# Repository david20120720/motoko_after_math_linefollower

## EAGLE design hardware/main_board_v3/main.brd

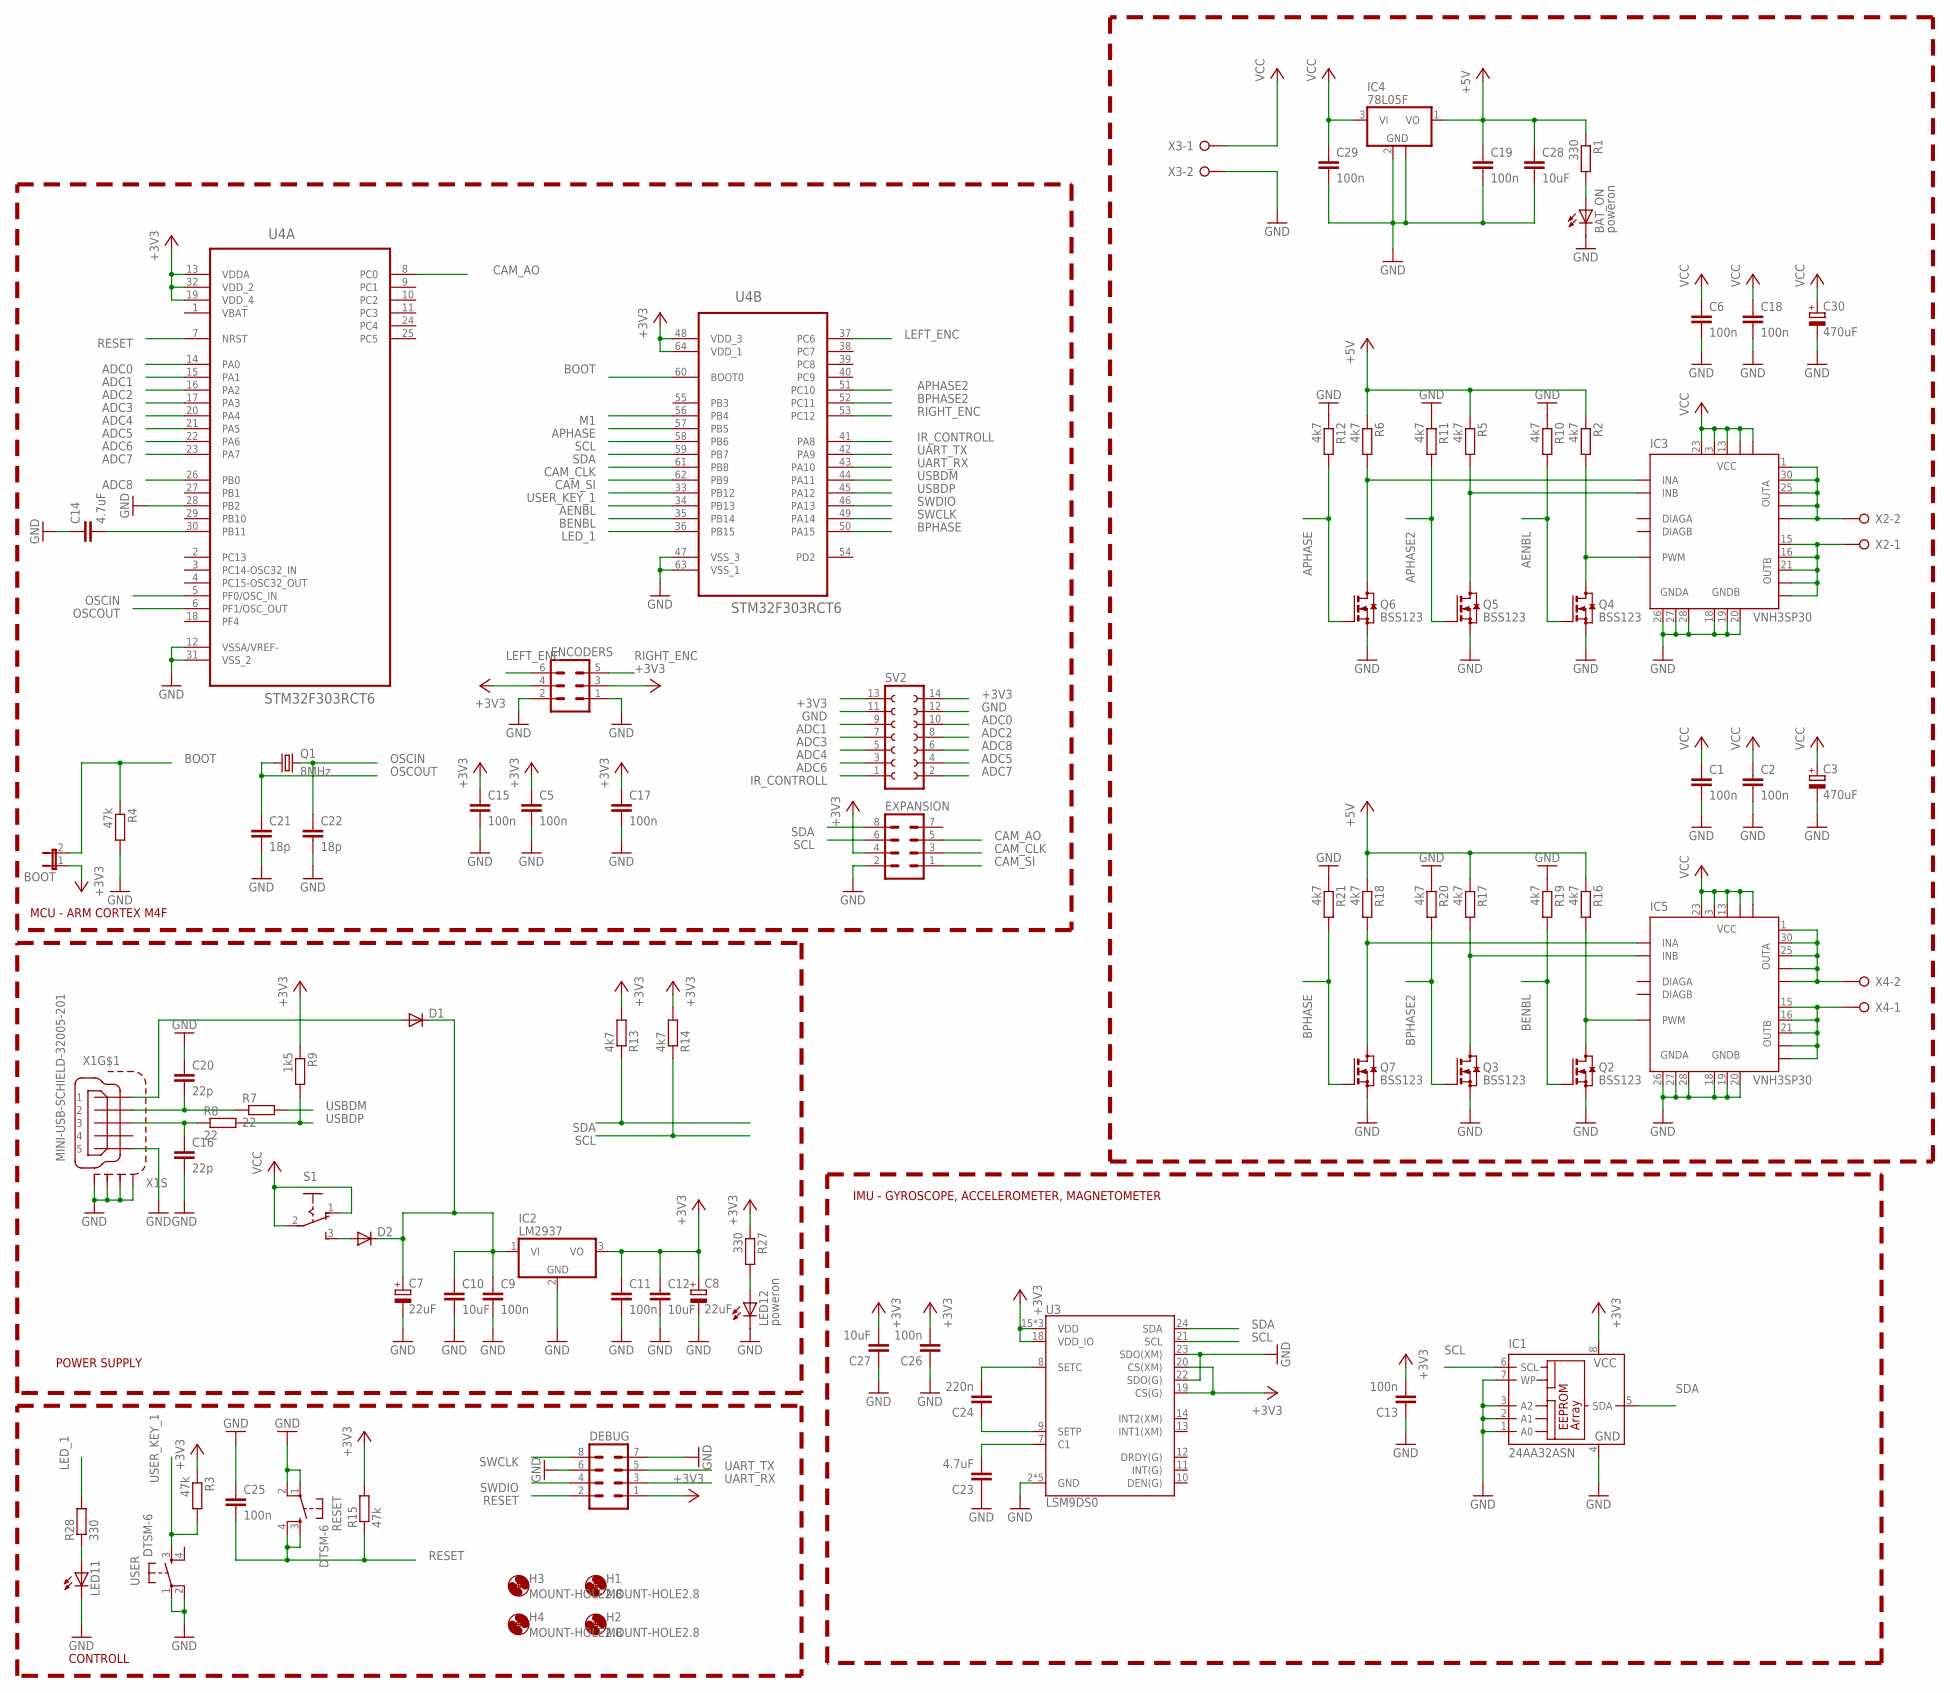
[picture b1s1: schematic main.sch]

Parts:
BAT_ON: poweron; CHIPLED_1206
BOOT: JP1E; JP1
C1, C2, C5, C6, C9, C11, C13, C15, C17, C18, C19, C25, C26, C29: 100n; C0805
C3, C30: 470uF; 140CLH-1014
C7, C8: 22uF; 153CLV-0505
C10, C12, C27, C28: 10uF; C0805
C14, C23: 4.7uF; C0805
C16, C20: 22p; C0805
C21, C22: 18p; C0805
C24: 220n; C0805
D1, D2: DIODE-SMB; SMB
DEBUG: MA04-2
ENCODERS: MA03-2
EXPANSION: MA04-2
H1, H2, H3, H4: MOUNT-HOLE2.8; 2,8
IC1: 24AA32ASN; SO-08
IC2: LM2937; TO263-3
IC3, IC5: VNH3SP30; MULTIPOWERSO-30
IC4: 78L05F; SOT89
LED11: LEDCHIPLED_1206; CHIPLED_1206
LED12: poweron; CHIPLED_1206
Q1: 8MHz; CTS406
Q2, Q3, Q4, Q5, Q6, Q7: BSS123; SOT23
R1, R27, R28: 330; M0805
R2, R5, R6, R10, R11, R12, R13, R14, R16, R17, R18, R19, R20, R21: 4k7; M0805
R3, R4, R15: 47k; M0805
R7, R8: 22; M0805
R9: 1k5; M0805
RESET: DTSM-6
S1: 255SB
SV2: FE07-2
U3: LSM9DS0; LGA-24
U4: STM32F303RCT6; QFP50P1200X1200X160-64N
USER: DTSM-6
X1: MINI-USB-SCHIELD-32005-201; 32005-201
X2, X3, X4: W237-02P; W237-132

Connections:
+3V3: BOOT.1, C5.1, C8.+, C11.1, C12.1, C13.2, C15.1, C17.1, C26.2, C27.2, DEBUG.1, ENCODERS.3, ENCODERS.4, EXPANSION.4, IC1.8 (VCC), IC2.3 (VO), R3.1, R9.1, R13.2, R14.2, R15.2, R27.1, SV2.13, SV2.14, U3.15 (VDD), U3.16 (VDD), U3.17 (VDD), U3.18 (VDD_IO), U3.19 (CS(G)), U3.20 (CS(XM)), U4.13 (VDDA), U4.19 (VDD_4), U4.32 (VDD_2), U4.48 (VDD_3), U4.64 (VDD_1)
+5V: C19.1, C28.1, IC4.1 (VO), R1.1, R2.1, R5.1, R6.1, R16.1, R17.1, R18.1; also elsewhere on the board
ADC0: SV2.10, U4.14 (PA0)
ADC1: SV2.9, U4.15 (PA1)
ADC2: SV2.8, U4.16 (PA2)
ADC3: SV2.7, U4.17 (PA3)
ADC4: SV2.5, U4.20 (PA4)
ADC5: SV2.4, U4.21 (PA5)
ADC6: SV2.3, U4.22 (PA6)
ADC7: SV2.2, U4.23 (PA7)
ADC8: SV2.6, U4.26 (PB0)
AENBL: Q4.1 (G), R10.2, U4.34 (PB13)
APHASE: Q6.1 (G), R12.2, U4.57 (PB5)
APHASE2: Q5.1 (G), R11.2, U4.51 (PC10)
BENBL: Q2.1 (G), R19.2, U4.35 (PB14)
BOOT: BOOT.2, R4.1, U4.60 (BOOT0)
BPHASE: Q7.1 (G), R21.2, U4.50 (PA15), U4.54 (PD2)
BPHASE2: Q3.1 (G), R20.2, U4.52 (PC11)
CAM_AO: EXPANSION.5, U4.8 (PC0)
CAM_CLK: EXPANSION.3, U4.61 (PB8)
CAM_SI: EXPANSION.1, U4.62 (PB9)
GND: BAT_ON.C, C1.2, C2.2, C3.-, C5.2, C6.2, C7.-, C8.-, C9.2, C10.2, C11.2, C12.2, C13.1, C14.1, C15.2, C16.2, C17.2, C18.2, C19.2, C20.1, C21.2, C22.2, C23.1, C25.1, C26.1, C27.1, C28.2, C29.2, C30.-, DEBUG.6, DEBUG.7, ENCODERS.1, ENCODERS.2, EXPANSION.2, IC1.1 (A0), IC1.2 (A1), IC1.3 (A2), IC1.4 (GND), IC1.7 (WP), IC2.2 (GND), IC3.18 (GNDB), IC3.19 (GNDB), IC3.20 (GNDB), IC3.26 (GNDA), IC3.27 (GNDA), IC3.28 (GNDA), IC4.2 (GND), IC4.2@1 (GND), IC5.18 (GNDB), IC5.19 (GNDB), IC5.20 (GNDB), IC5.26 (GNDA), IC5.27 (GNDA), IC5.28 (GNDA), LED11.C, LED12.C, Q2.2 (S), Q3.2 (S), Q4.2 (S), Q5.2 (S), Q6.2 (S), Q7.2 (S), R4.2, R10.1, R11.1, R12.1, R19.1, R20.1, R21.1, RESET.1, RESET.2, SV2.11, SV2.12, U3.2 (GND), U3.3 (GND), U3.4 (GND), U3.5 (GND), U3.6 (GND), U3.22 (SDO(G)), U3.23 (SDO(XM)), U4.12 (VSSA/VREF-), U4.28 (PB2), U4.31 (VSS_2), U4.47 (VSS_3), U4.63 (VSS_1), USER.1, USER.2, X1.5, X1.M1 (S1), X1.M2 (S2), X1.M3 (S3), X1.M4 (S4), X3.2; also elsewhere on the board
IR_CONTROLL: SV2.1, U4.41 (PA8)
LED_1: R28.2, U4.36 (PB15)
LEFT_ENC: ENCODERS.6, U4.37 (PC6)
M1: U4.56 (PB4)
MOTOR_ENABLE: U4.38 (PC7); also elsewhere on the board
M_ENABLE: IC3.6 (DIAGA), IC3.10 (DIAGB), IC5.6 (DIAGA), IC5.10 (DIAGB); also elsewhere on the board
unnamed: D2.A, S1.3 (S)
unnamed: C7.+, C9.1, C10.1, D1.C, D2.C, IC2.1 (VI)
unnamed: BAT_ON.A, R1.2
unnamed: IC5.5 (INA), Q7.3 (D), R18.2
unnamed: IC5.11 (INB), Q3.3 (D), R17.2
unnamed: C23.2, U3.7 (C1)
unnamed: C24.2, U3.8 (SETC)
unnamed: IC5.8 (PWM), Q2.3 (D), R16.2
unnamed: IC5.1 (OUTA), IC5.25 (OUTA), IC5.30 (OUTA), IC5.OUTA, IC5.OUTA@1 (OUTA), X4.2
unnamed: C24.1, U3.9 (SETP)
unnamed: IC5.15 (OUTB), IC5.16 (OUTB), IC5.21 (OUTB), IC5.OUTB, IC5.OUTB@1 (OUTB), X4.1
unnamed: C14.2, U4.30 (PB11)
unnamed: IC3.5 (INA), Q6.3 (D), R6.2
unnamed: IC3.11 (INB), Q5.3 (D), R5.2
unnamed: IC3.8 (PWM), Q4.3 (D), R2.2
unnamed: IC3.1 (OUTA), IC3.25 (OUTA), IC3.30 (OUTA), IC3.OUTA, IC3.OUTA@1 (OUTA), X2.2
unnamed: LED12.A, R27.2
unnamed: IC3.15 (OUTB), IC3.16 (OUTB), IC3.21 (OUTB), IC3.OUTB, IC3.OUTB@1 (OUTB), X2.1
unnamed: LED11.A, R28.1
unnamed: C20.2, R7.1, X1.2
unnamed: C16.1, R8.1, X1.3
unnamed: D1.A, X1.1
OSCIN: C22.1, Q1.3 (2), U4.5 (PF0/OSC_IN)
OSCOUT: C21.1, Q1.1, U4.6 (PF1/OSC_OUT)
RESET: C25.2, DEBUG.2, R15.1, RESET.3, RESET.4, U4.7 (NRST)
RIGHT_ENC: ENCODERS.5, U4.53 (PC12)
SCL: EXPANSION.6, IC1.6 (SCL), R14.1, U3.21 (SCL), U4.58 (PB6)
SDA: EXPANSION.8, IC1.5 (SDA), R13.1, U3.24 (SDA), U4.59 (PB7)
SWCLK: DEBUG.8, U4.49 (PA14)
SWDIO: DEBUG.4, U4.46 (PA13)
UART_RX: DEBUG.3, U4.43 (PA10)
UART_TX: DEBUG.5, U4.42 (PA9)
USBDM: R7.2, U4.44 (PA11)
USBDP: R8.2, R9.2, U4.45 (PA12)
USER_KEY_1: R3.2, U4.33 (PB12), USER.3
VBAT: U4.1 (VBAT)
VCC: C1.1, C2.1, C3.+, C6.1, C18.1, C29.1, C30.+, IC3.3 (VCC), IC3.13 (VCC), IC3.23 (VCC), IC3.VCC, IC3.VCC@1 (VCC), IC4.3 (VI), IC5.3 (VCC), IC5.13 (VCC), IC5.23 (VCC), IC5.VCC, IC5.VCC@1 (VCC), S1.1 (O), S1.2, X3.1

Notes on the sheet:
POWER SUPPLY
CONTROLL
MCU - ARM CORTEX M4F
IMU - GYROSCOPE, ACCELEROMETER, MAGNETOMETER

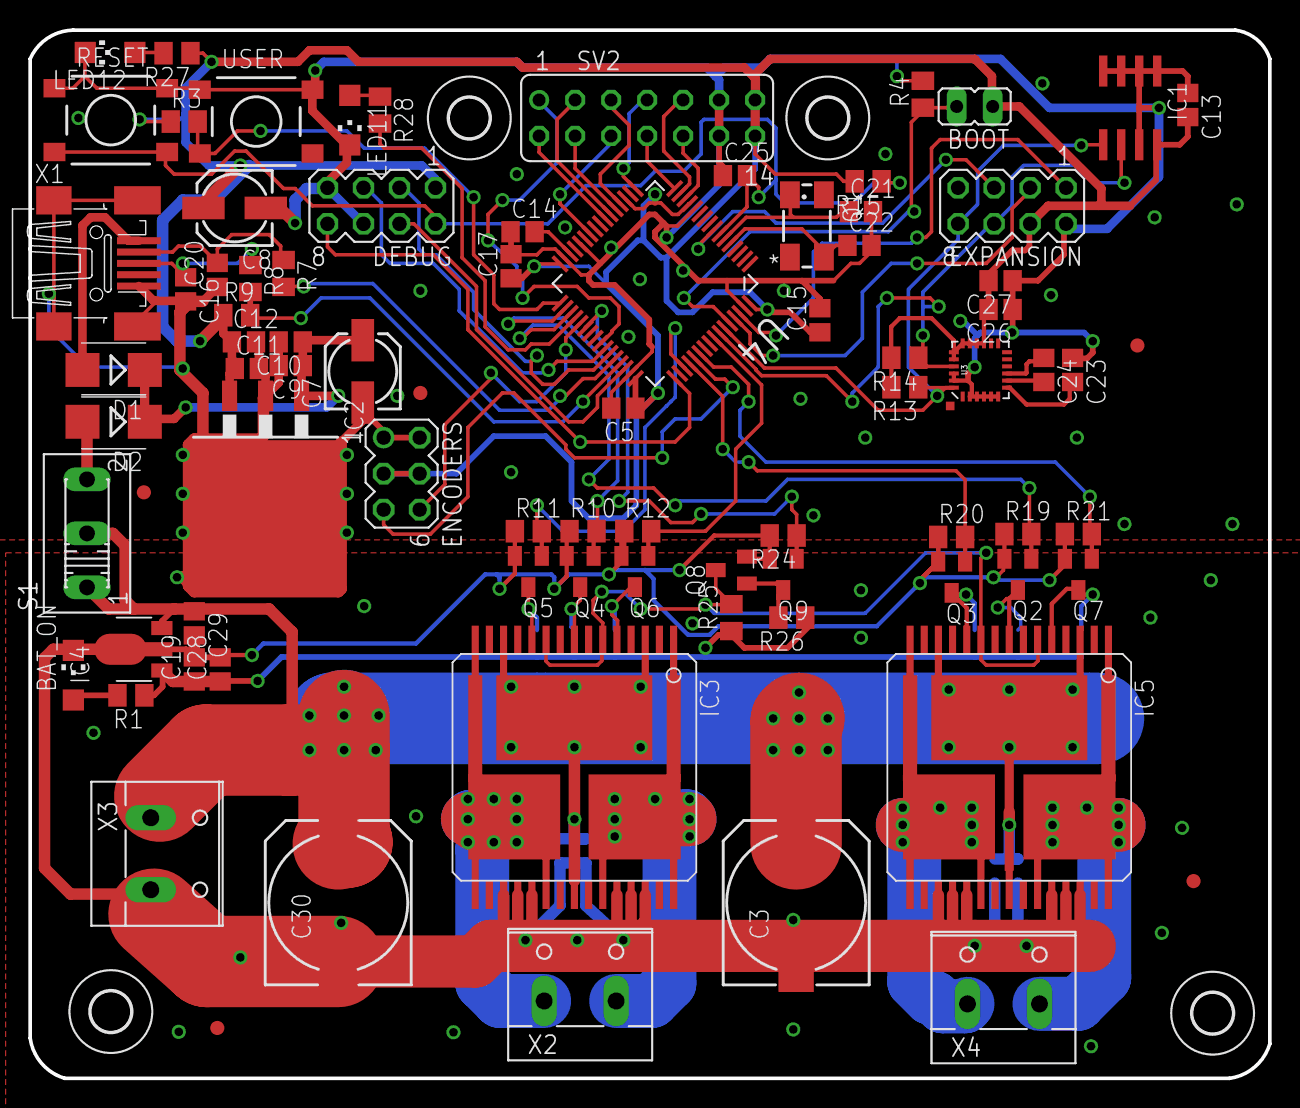
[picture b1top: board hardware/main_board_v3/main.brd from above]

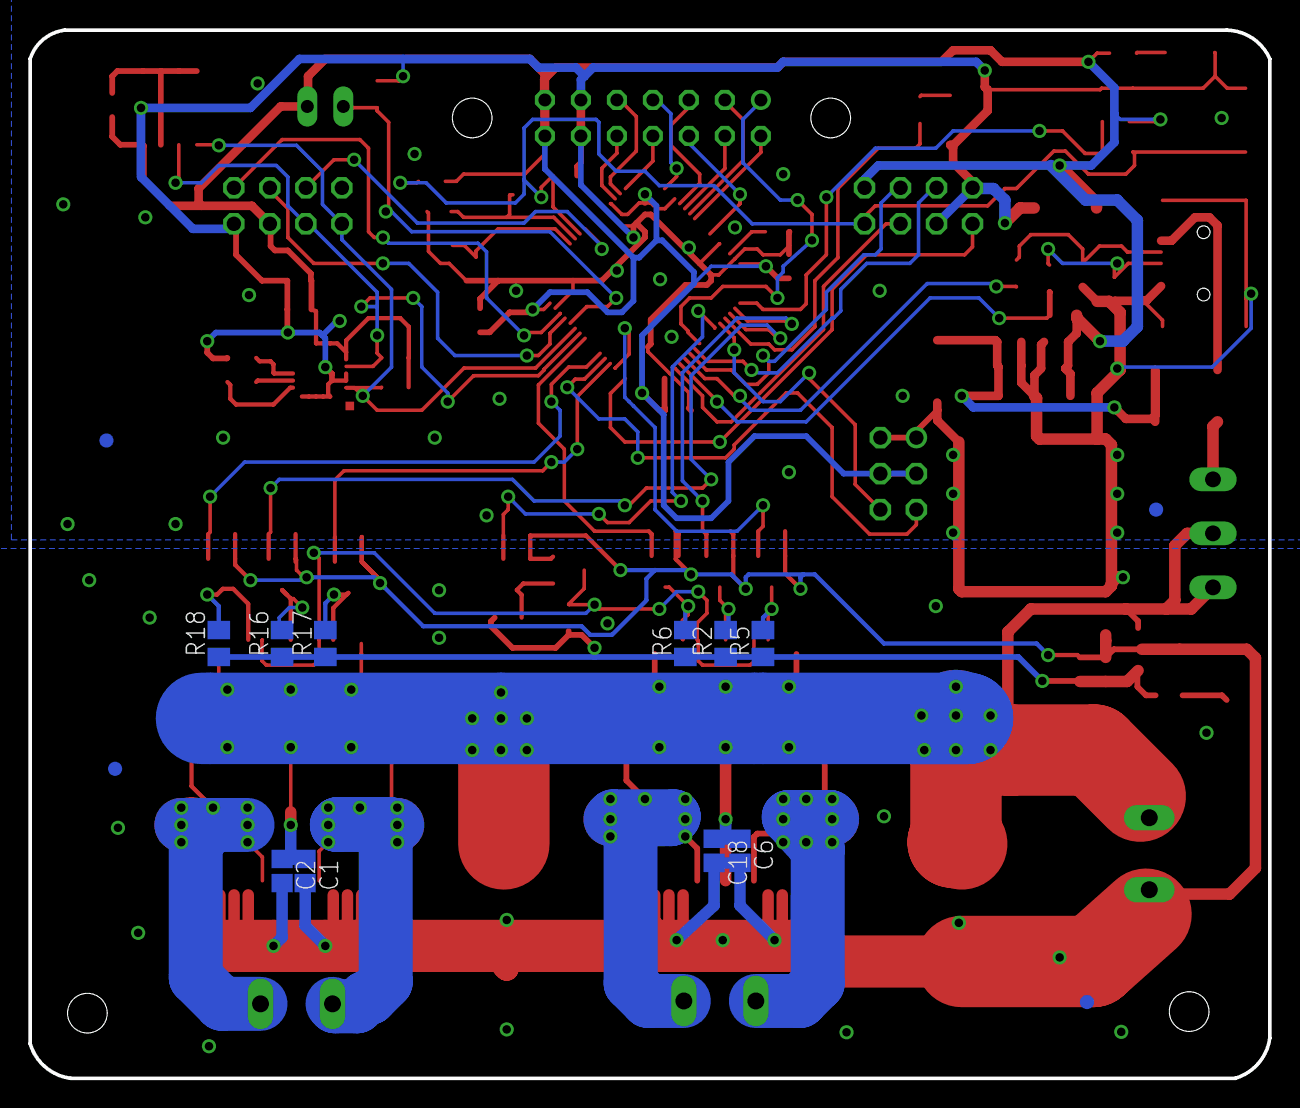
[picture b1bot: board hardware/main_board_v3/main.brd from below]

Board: 2 copper layers, 87.5 x 74.0 mm, 101 parts (14 on the bottom side), 64 nets.

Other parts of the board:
Q8, Q9: BSS123; SOT23
R24, R25, R26: 4k7; M0805
U$1, U$2, U$3, U$4, U$5, U$6, U$7, U$8, U$9: FIDUCIAL; FIDUCIAL_1MM

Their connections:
+5V: R25.1, R26.1; also elsewhere on the board
GND: Q8.2, Q9.2, R24.2; also elsewhere on the board
MOTOR_ENABLE: Q9.1, R24.1; also elsewhere on the board
M_ENABLE: Q8.3, R25.2; also elsewhere on the board
unnamed: Q8.1, Q9.3, R26.2

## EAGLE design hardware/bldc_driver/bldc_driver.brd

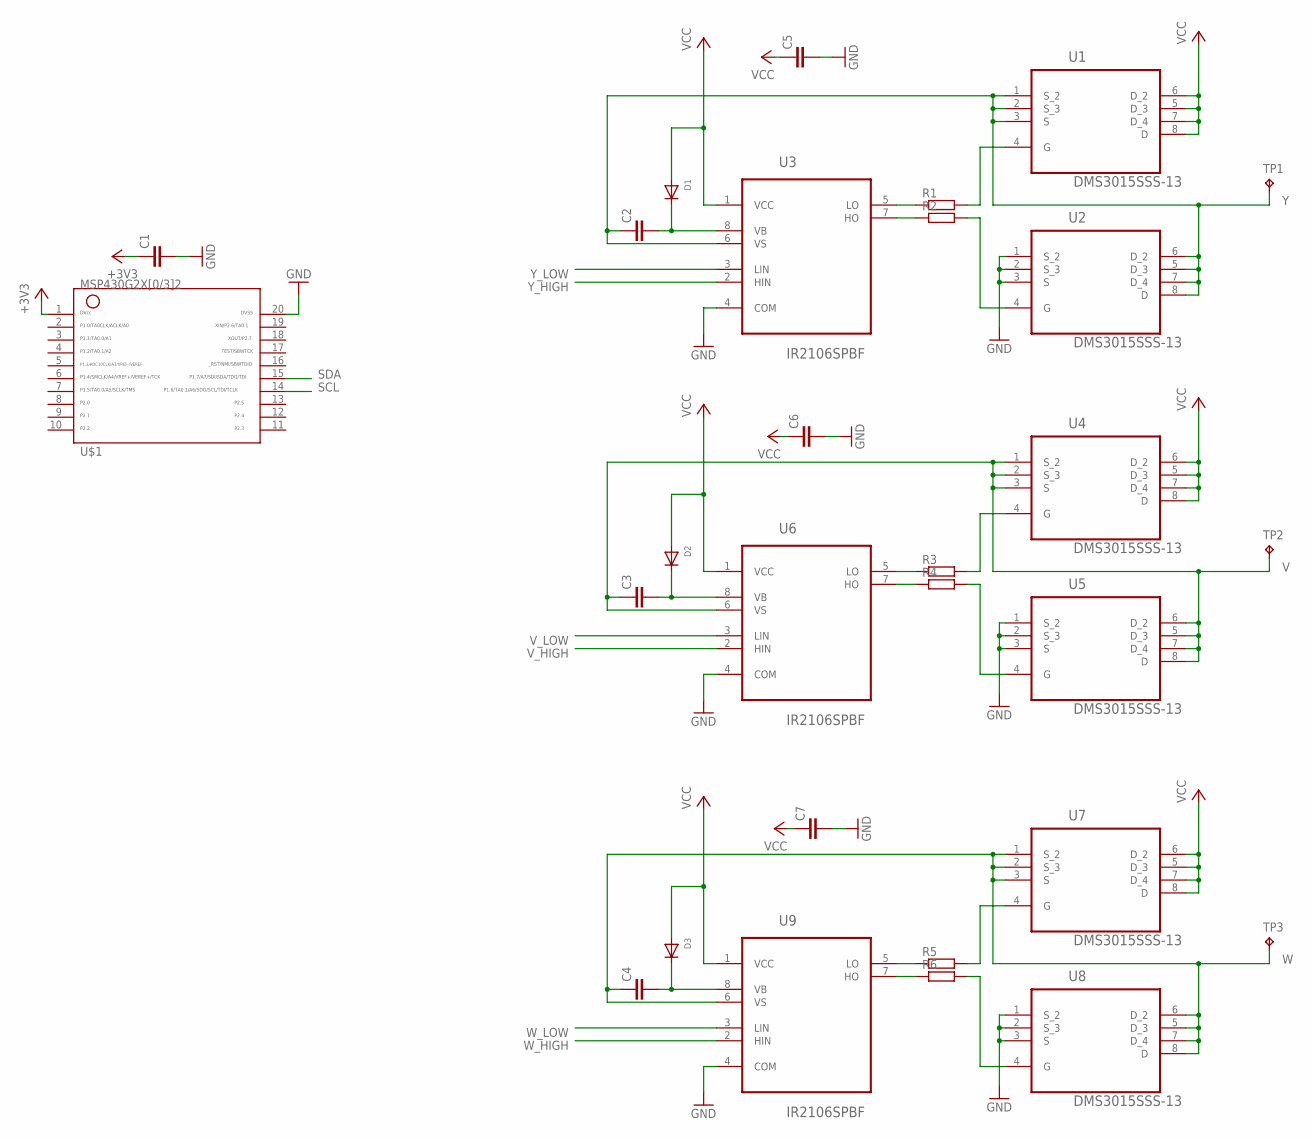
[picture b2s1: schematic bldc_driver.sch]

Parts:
C1, C2, C3, C4, C5, C6, C7: C-EUC0805; C0805
D1, D2, D3: DIODE_SOD-123FL; SOD-123FL
R1, R2, R3, R4, R5, R6: R-EU_M0805; M0805
TP1, TP2, TP3: TPTP18R; TP18R
U1, U2, U4, U5, U7, U8: DMS3015SSS-13; SOIC127P600X175-8N
U3, U6, U9: IR2106SPBF; SOIC127P600X175-8N
U$1: G2X[0/3]2---PW20; PW20

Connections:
+3V3: C1.1, U$1.1
GND: C1.2, C5.2, C6.2, C7.2, U2.1 (S_2), U2.2 (S_3), U2.3 (S), U3.4 (COM), U5.1 (S_2), U5.2 (S_3), U5.3 (S), U6.4 (COM), U8.1 (S_2), U8.2 (S_3), U8.3 (S), U9.4 (COM), U$1.20
unnamed: R1.2, U1.4 (G)
unnamed: R1.1, U3.5 (LO)
unnamed: R2.1, U3.7 (HO)
unnamed: R2.2, U2.4 (G)
unnamed: C2.2, D1.C, U3.8 (VB)
unnamed: R3.2, U4.4 (G)
unnamed: R3.1, U6.5 (LO)
unnamed: R4.1, U6.7 (HO)
unnamed: R4.2, U5.4 (G)
unnamed: C3.2, D2.C, U6.8 (VB)
unnamed: R5.2, U7.4 (G)
unnamed: R5.1, U9.5 (LO)
unnamed: R6.1, U9.7 (HO)
unnamed: R6.2, U8.4 (G)
unnamed: C4.2, D3.C, U9.8 (VB)
SCL: U$1.14
SDA: U$1.15
V: C3.1, TP2.TP, U4.1 (S_2), U4.2 (S_3), U4.3 (S), U5.5 (D_3), U5.6 (D_2), U5.7 (D_4), U5.8 (D), U6.6 (VS)
VCC: C5.1, C6.1, C7.1, D1.A, D2.A, D3.A, U1.5 (D_3), U1.6 (D_2), U1.7 (D_4), U1.8 (D), U3.1 (VCC), U4.5 (D_3), U4.6 (D_2), U4.7 (D_4), U4.8 (D), U6.1 (VCC), U7.5 (D_3), U7.6 (D_2), U7.7 (D_4), U7.8 (D), U9.1 (VCC)
V_HIGH: U6.2 (HIN)
V_LOW: U6.3 (LIN)
W: C4.1, TP3.TP, U7.1 (S_2), U7.2 (S_3), U7.3 (S), U8.5 (D_3), U8.6 (D_2), U8.7 (D_4), U8.8 (D), U9.6 (VS)
W_HIGH: U9.2 (HIN)
W_LOW: U9.3 (LIN)
Y: C2.1, TP1.TP, U1.1 (S_2), U1.2 (S_3), U1.3 (S), U2.5 (D_3), U2.6 (D_2), U2.7 (D_4), U2.8 (D), U3.6 (VS)
Y_HIGH: U3.2 (HIN)
Y_LOW: U3.3 (LIN)

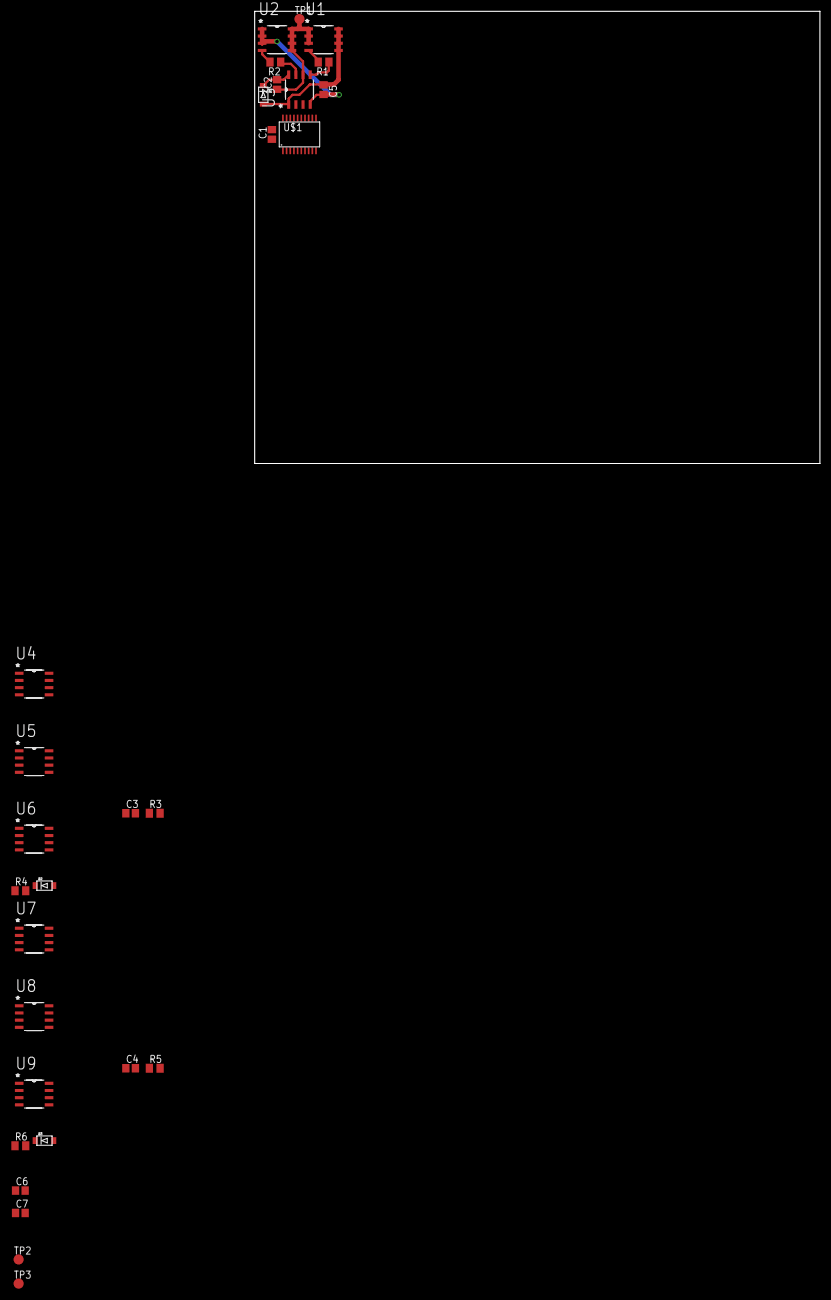
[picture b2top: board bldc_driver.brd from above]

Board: 2 copper layers, 100.0 x 80.0 mm, 29 parts (0 on the bottom side), 21 nets.

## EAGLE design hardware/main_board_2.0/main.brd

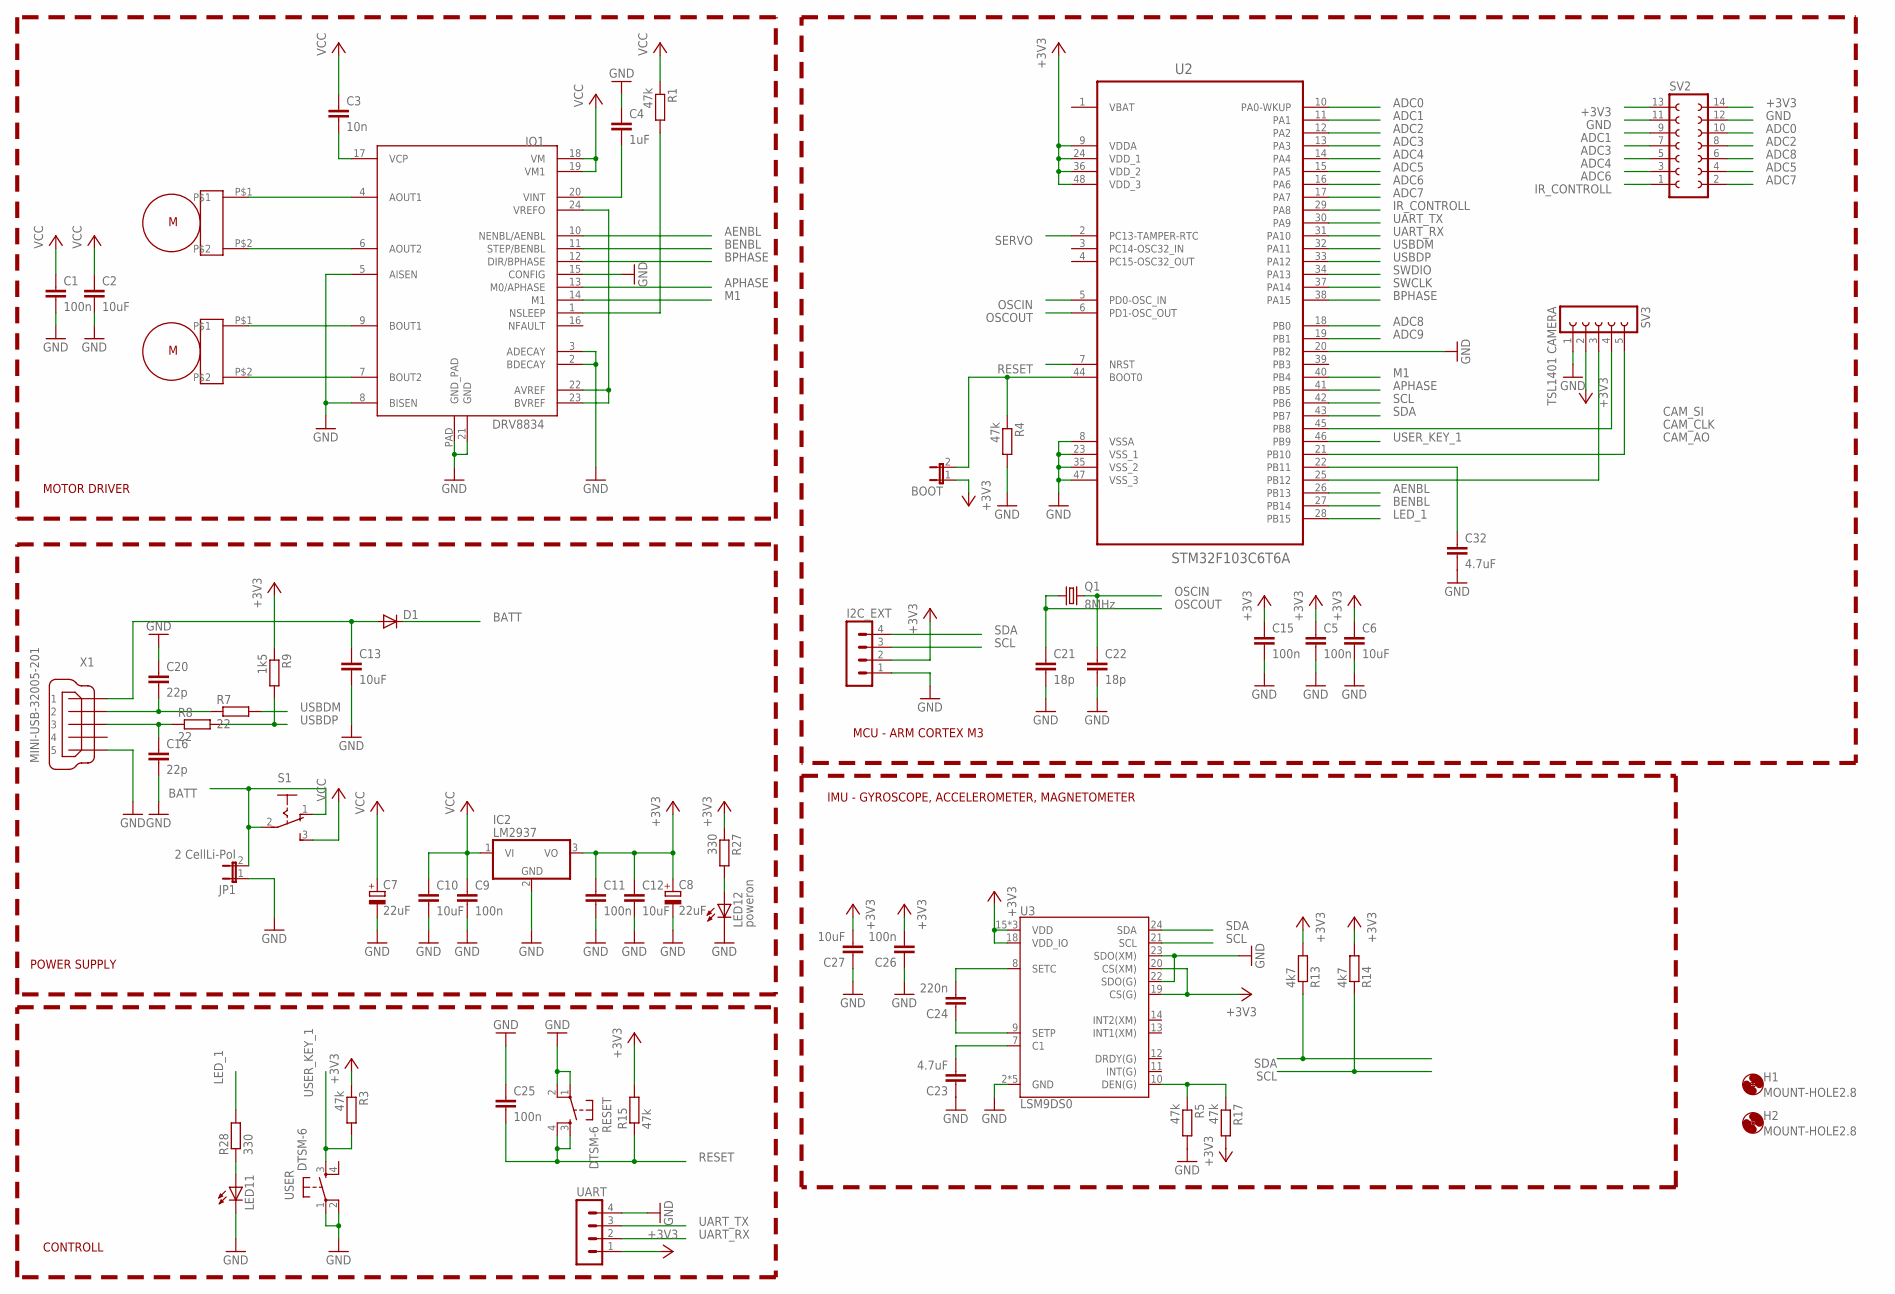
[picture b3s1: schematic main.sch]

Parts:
BOOT: JP1E; JP1
C1: 100n; C1206
C2: 10uF; C1206
C3: 10n; C1206
C4: 1uF; C1206
C5, C9, C11, C15, C25, C26: 100n; C0805
C6, C10, C12, C13, C27: 10uF; C0805
C7, C8: 22uF; 153CLV-0505
C16, C20: 22p; C0805
C21, C22: 18p; C0805
C23, C32: 4.7uF; C0805
C24: 220n; C0805
D1: DIODE-SMB; SMB
H1, H2: MOUNT-HOLE2.8; 2,8
I2C_EXT: MA04-1
IC2: LM2937; TO263-3
IO1: DRV8834; DRV8834_PCK
JP1: 2 CellLi-Pol; JP1
LED11: LEDCHIPLED_1206; CHIPLED_1206
LED12: poweron; CHIPLED_1206
Q1: 8MHz; CTS406
R1: 47k; M1206
R3, R4, R5, R15, R17: 47k; M0805
R7, R8: 22; M0805
R9: 1k5; M0805
R13, R14: 4k7; M0805
R27, R28: 330; M0805
RESET: DTSM-6
S1: 255SB
SV2: FE07-2
SV3: TSL1401 CAMERA; FE05-1
U2: STM32F103C6T6A; QFP50P900X900X160-48N
U3: LSM9DS0; LGA-24
U$1, U$2: MICRO_METAL_GEAR_MOTOR
UART: MA04-1
USER: DTSM-6
X1: MINI-USB-32005-201; 32005-201

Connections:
+3V3: BOOT.1, C5.1, C6.1, C8.+, C11.1, C12.1, C15.1, C26.2, C27.2, I2C_EXT.2, IC2.3 (VO), R3.1, R9.1, R13.2, R14.2, R15.2, R17.2, R27.1, SV2.13, SV2.14, SV3.2, U2.9 (VDDA), U2.24 (VDD_1), U2.36 (VDD_2), U2.48 (VDD_3), U3.15 (VDD), U3.16 (VDD), U3.17 (VDD), U3.18 (VDD_IO), U3.19 (CS(G)), U3.20 (CS(XM)), UART.1
ADC0: SV2.10, U2.10 (PA0-WKUP)
ADC1: SV2.9, U2.11 (PA1)
ADC2: SV2.8, U2.12 (PA2)
ADC3: SV2.7, U2.13 (PA3)
ADC4: SV2.5, U2.14 (PA4)
ADC5: SV2.4, U2.15 (PA5)
ADC6: SV2.3, U2.16 (PA6)
ADC7: SV2.2, U2.17 (PA7)
ADC8: SV2.6, U2.18 (PB0)
ADC9: U2.19 (PB1)
AENBL: IO1.10 (NENBL/AENBL), U2.26 (PB13)
APHASE: IO1.13 (M0/APHASE), U2.41 (PB5)
BATT: D1.C, JP1.2, S1.1 (O), S1.2
BENBL: IO1.11 (STEP/BENBL), U2.27 (PB14)
BPHASE: IO1.12 (DIR/BPHASE), U2.38 (PA15)
CAM_AO: SV3.3, U2.25 (PB12)
CAM_CLK: SV3.4, U2.45 (PB8)
CAM_SI: SV3.5, U2.21 (PB10)
GND: C1.2, C2.2, C4.1, C5.2, C6.2, C7.-, C8.-, C9.2, C10.2, C11.2, C12.2, C13.2, C15.2, C16.2, C20.1, C21.2, C22.2, C23.1, C25.1, C26.1, C27.1, C32.2, I2C_EXT.1, IC2.2 (GND), IO1.2 (BDECAY), IO1.3 (ADECAY), IO1.5 (AISEN), IO1.8 (BISEN), IO1.15 (CONFIG), IO1.21 (GND), IO1.PAD (GND_PAD), JP1.1, LED11.C, LED12.C, R4.2, R5.2, RESET.1, RESET.2, SV2.11, SV2.12, SV3.1, U2.8 (VSSA), U2.20 (PB2), U2.23 (VSS_1), U2.35 (VSS_2), U2.47 (VSS_3), U3.2 (GND), U3.3 (GND), U3.4 (GND), U3.5 (GND), U3.6 (GND), U3.22 (SDO(G)), U3.23 (SDO(XM)), UART.4, USER.1, USER.2, X1.5
IR_CONTROLL: SV2.1, U2.29 (PA8)
LED_1: R28.2, U2.28 (PB15)
M1: IO1.14 (M1), U2.40 (PB4)
unnamed: IO1.4 (AOUT1), U$1.P$1
unnamed: IO1.6 (AOUT2), U$1.P$2
unnamed: IO1.9 (BOUT1), U$2.P$1
unnamed: IO1.7 (BOUT2), U$2.P$2
unnamed: C3.2, IO1.17 (VCP)
unnamed: C23.2, U3.7 (C1)
unnamed: C24.2, U3.8 (SETC)
unnamed: IO1.22 (AVREF), IO1.23 (BVREF), IO1.24 (VREFO)
unnamed: IO1.1 (NSLEEP), R1.2
unnamed: C24.1, U3.9 (SETP)
unnamed: C32.1, U2.22 (PB11)
unnamed: BOOT.2, R4.1, U2.44 (BOOT0)
unnamed: R5.1, R17.1, U3.10 (DEN(G))
unnamed: C4.2, IO1.20 (VINT)
unnamed: LED12.A, R27.2
unnamed: LED11.A, R28.1
unnamed: C20.2, R7.1, X1.2
unnamed: C16.1, R8.1, X1.3
unnamed: C13.1, D1.A, X1.1
OSCIN: C22.1, Q1.3 (2), U2.5 (PD0-OSC_IN)
OSCOUT: C21.1, Q1.1, U2.6 (PD1-OSC_OUT)
RESET: C25.2, R15.1, RESET.3, RESET.4, U2.7 (NRST)
SCL: I2C_EXT.3, R14.1, U2.42 (PB6), U3.21 (SCL)
SDA: I2C_EXT.4, R13.1, U2.43 (PB7), U3.24 (SDA)
SERVO: U2.2 (PC13-TAMPER-RTC)
SWCLK: U2.37 (PA14)
SWDIO: U2.34 (PA13)
UART_RX: U2.31 (PA10), UART.2
UART_TX: U2.30 (PA9), UART.3
USBDM: R7.2, U2.32 (PA11)
USBDP: R8.2, R9.2, U2.33 (PA12)
USER_KEY_1: R3.2, U2.46 (PB9), USER.3
VBAT: U2.1 (VBAT)
VCC: C1.1, C2.1, C3.1, C7.+, C9.1, C10.1, IC2.1 (VI), IO1.18 (VM), IO1.19 (VM1), R1.1, S1.3 (S)

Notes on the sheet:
MOTOR DRIVER
POWER SUPPLY
CONTROLL
MCU - ARM CORTEX M3
IMU - GYROSCOPE, ACCELEROMETER, MAGNETOMETER

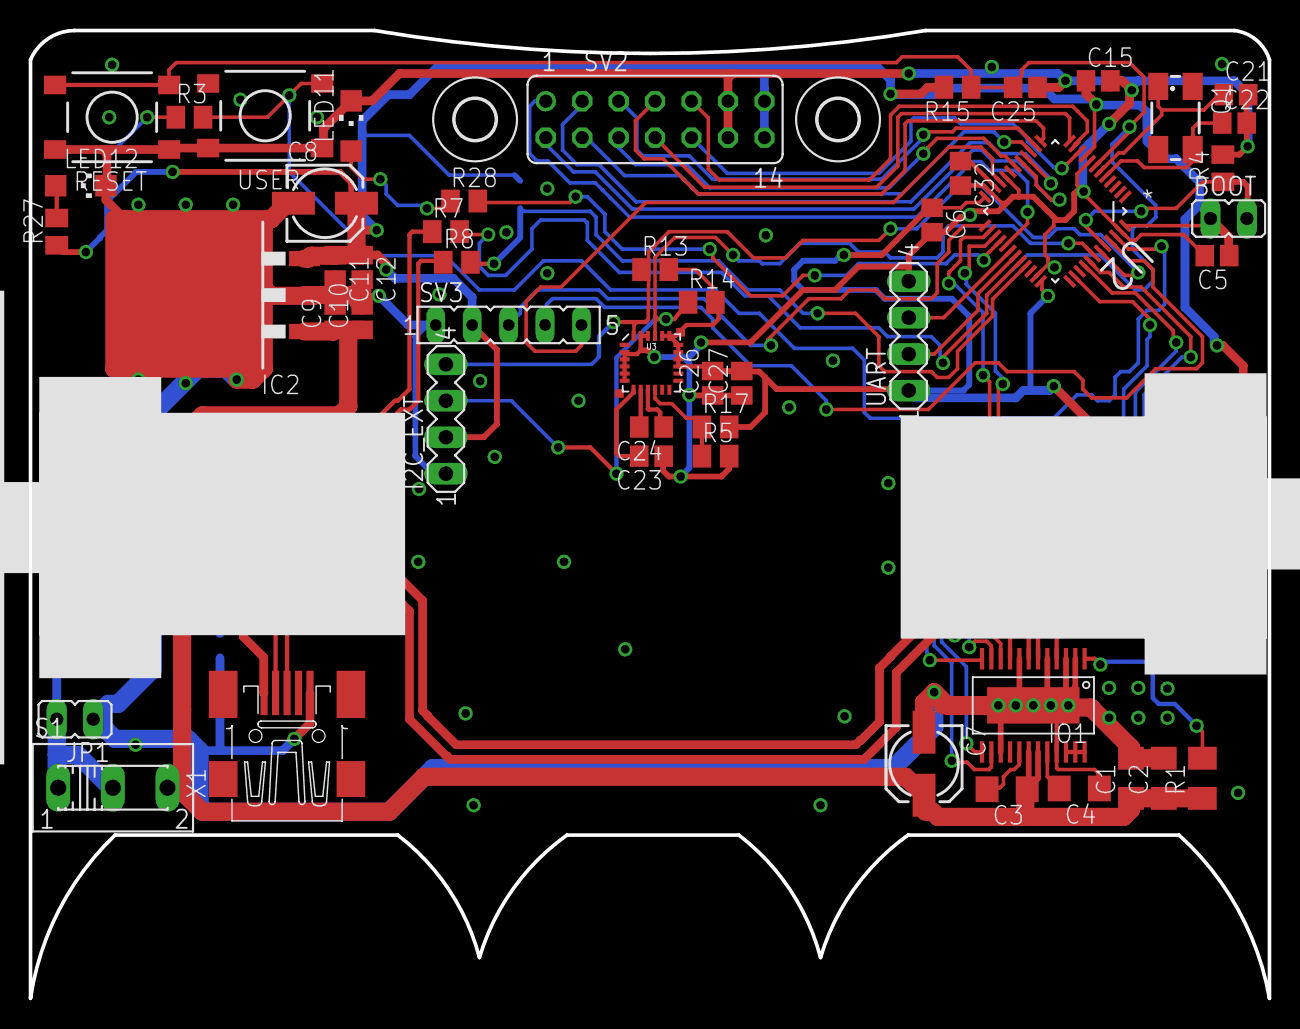
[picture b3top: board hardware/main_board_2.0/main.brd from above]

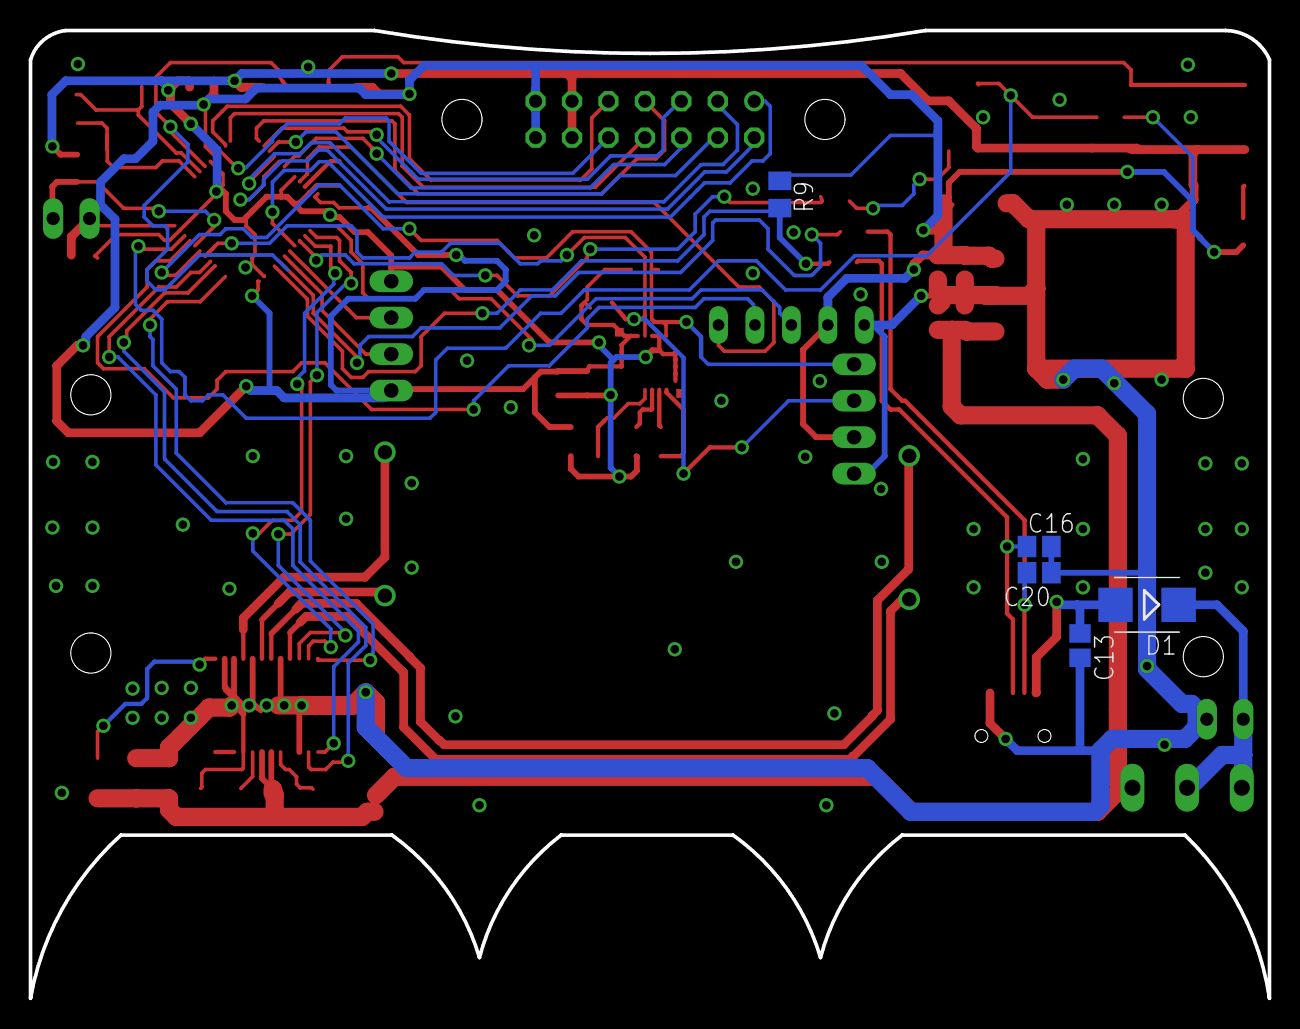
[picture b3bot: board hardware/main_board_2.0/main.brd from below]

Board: 2 copper layers, 86.4 x 67.5 mm, 59 parts (5 on the bottom side), 52 nets.

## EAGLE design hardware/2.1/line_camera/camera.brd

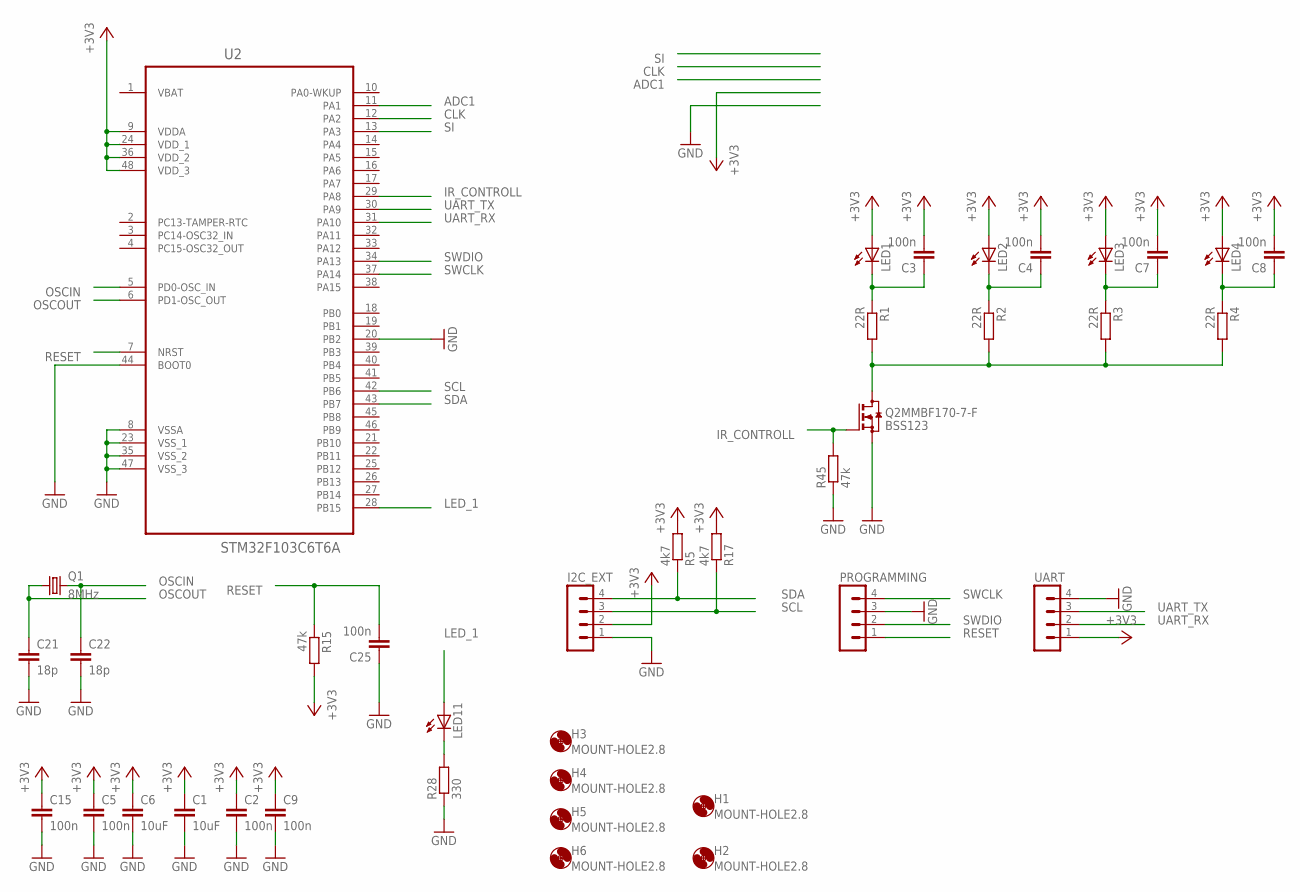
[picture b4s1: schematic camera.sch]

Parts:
C1, C6: 10uF; C0805
C2, C3, C4, C5, C7, C8, C9, C15, C25: 100n; C0805
C21, C22: 18p; C0805
H1, H2, H3, H4, H5, H6: MOUNT-HOLE2.8; 2,8
I2C_EXT: MA04-1
LED1, LED2, LED3, LED4: LED5MM
LED11: LEDCHIPLED_1206; CHIPLED_1206
PROGRAMMING: MA04-1
Q1: 8MHz; CTS406
Q2MMBF170-7-F: BSS123; SOT23
R1, R2, R3, R4: 22R; M0805
R5, R17: 4k7; M0805
R15, R45: 47k; M0805
R28: 330; M0805
U2: STM32F103C6T6A; QFP50P900X900X160-48N
UART: MA04-1

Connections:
+3V3: C1.1, C2.1, C3.2, C4.2, C5.1, C6.1, C7.2, C8.2, C9.1, C15.1, I2C_EXT.2, LED1.A, LED2.A, LED3.A, LED4.A, R5.2, R15.2, R17.2, U2.9 (VDDA), U2.24 (VDD_1), U2.36 (VDD_2), U2.48 (VDD_3), UART.1
ADC1: U2.11 (PA1)
CLK: U2.12 (PA2)
GND: C1.2, C2.2, C5.2, C6.2, C9.2, C15.2, C21.2, C22.2, C25.1, I2C_EXT.1, PROGRAMMING.3, Q2MMBF170-7-F.2 (S), R28.1, R45.1, U2.8 (VSSA), U2.20 (PB2), U2.23 (VSS_1), U2.35 (VSS_2), U2.44 (BOOT0), U2.47 (VSS_3), UART.4
IR_CONTROLL: Q2MMBF170-7-F.1 (G), R45.2, U2.29 (PA8)
LED_1: LED11.A, U2.28 (PB15)
unnamed: LED11.C, R28.2
unnamed: C3.1, LED1.K (C), R1.1
unnamed: C4.1, LED2.K (C), R2.1
unnamed: C7.1, LED3.K (C), R3.1
unnamed: C8.1, LED4.K (C), R4.1
unnamed: Q2MMBF170-7-F.3 (D), R1.2, R2.2, R3.2, R4.2
OSCIN: C22.1, Q1.3 (2), U2.5 (PD0-OSC_IN)
OSCOUT: C21.1, Q1.1, U2.6 (PD1-OSC_OUT)
RESET: C25.2, PROGRAMMING.1, R15.1, U2.7 (NRST)
SCL: I2C_EXT.3, R17.1, U2.42 (PB6)
SDA: I2C_EXT.4, R5.1, U2.43 (PB7)
SI: U2.13 (PA3)
SWCLK: PROGRAMMING.4, U2.37 (PA14)
SWDIO: PROGRAMMING.2, U2.34 (PA13)
UART_RX: U2.31 (PA10), UART.2
UART_TX: U2.30 (PA9), UART.3
VBAT: U2.1 (VBAT)
